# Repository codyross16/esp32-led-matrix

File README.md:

# ESP32 LED Matrix

Custom ESP32-S3 PCB with an 8x8 addressable LED matrix and push buttons, designed in KiCad and assembled by JLCPCB. Built to play simple one-button games like the Chrome Dino game.

Full schematic: [schematic.pdf](docs/schematic.pdf)

## Hardware
- ESP32-S3-MINI-1 (N8) microcontroller
- 64 SK6812MINI-E reverse-mount RGB LEDs in a serpentine chain
- USB-C power and programming, with 5.1k CC resistors
- SN74AHCT1G125 level shifter (3.3V to 5V LED data)
- AP7361C 3.3V LDO, SD05 TVS protection, 1000µF bulk cap
- 3 buttons: BOOT, RESET, and INPUT (game control)

## Repo layout
- `hardware/` KiCad project (schematic and PCB)
- `hardware/fab/` Gerbers, BOM, and CPL files for JLCPCB
- `firmware/` ESP32 code (coming soon)
- `docs/` Schematic PDF and images

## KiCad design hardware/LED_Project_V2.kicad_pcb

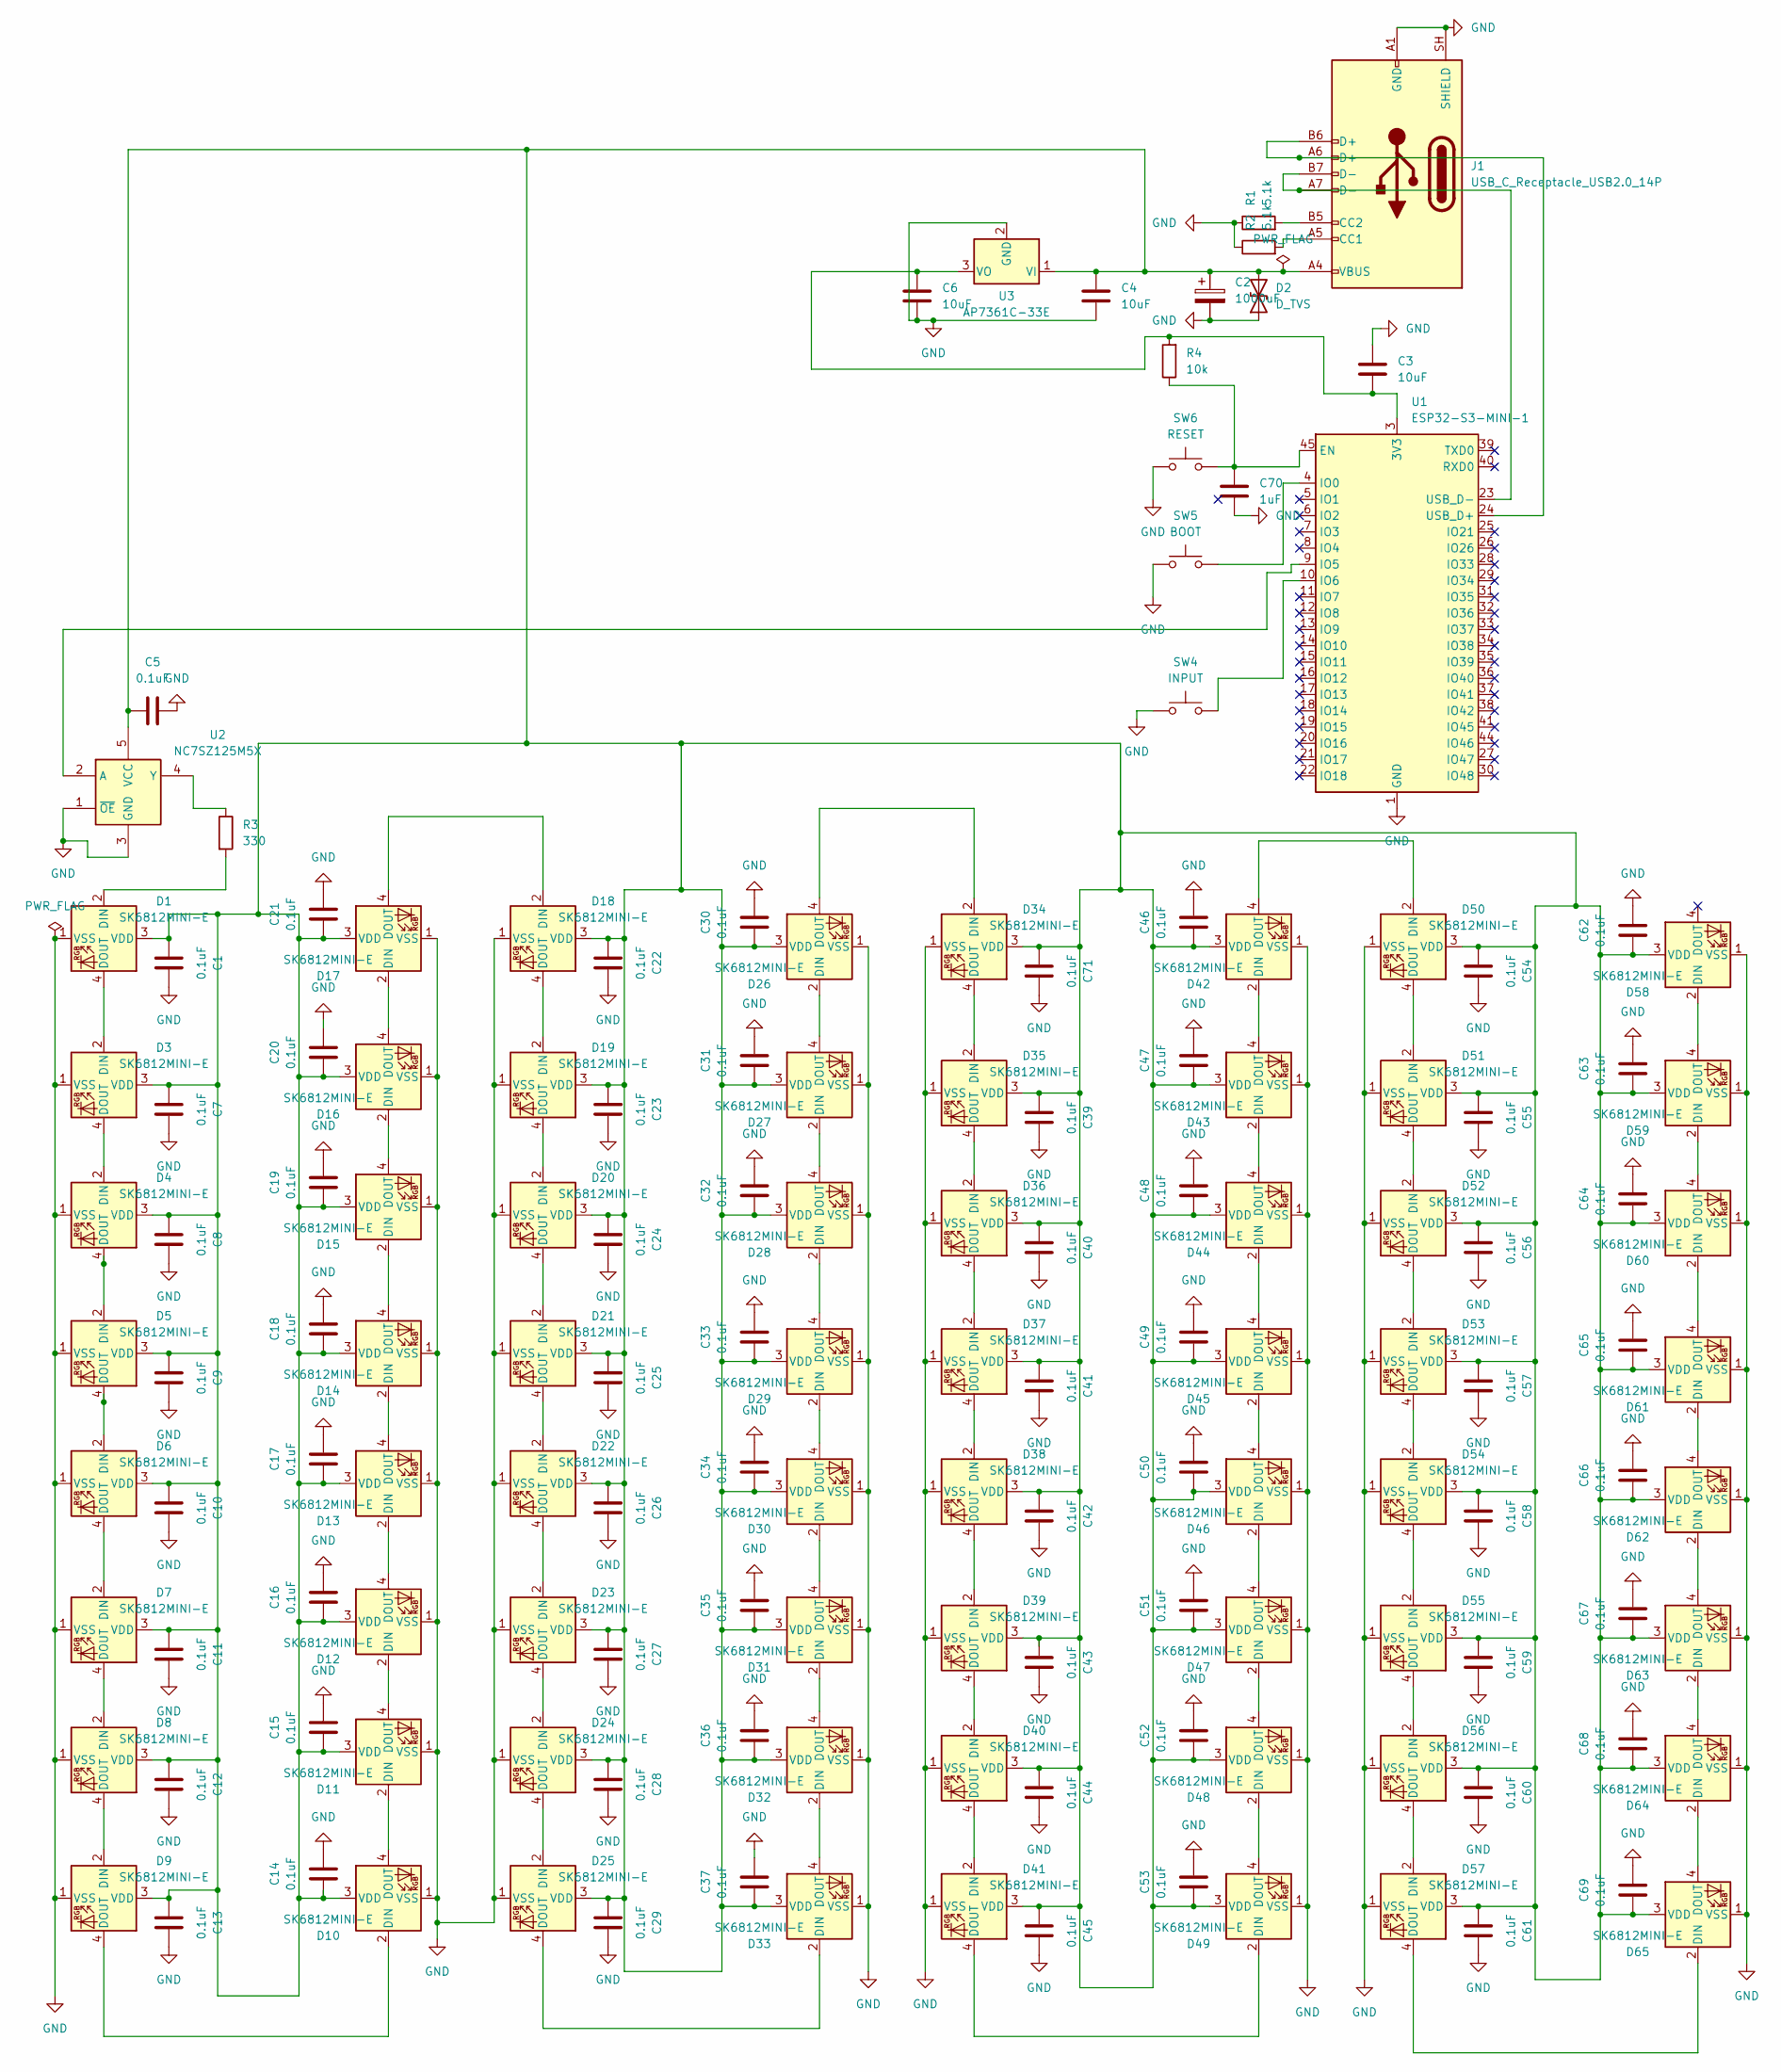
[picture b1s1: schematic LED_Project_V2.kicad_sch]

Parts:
C1, C5, C7, C8, C9, C10, C11, C12, C13, C14, C15, C16, C17, C18, C19, C20, C21, C22, C23, C24, C25, C26, C27, C28, C29, C30, C31, C32, C33, C34, C35, C36, C37, C39, C40, C41, C42, C43, C44, C45, C46, C47, C48, C49, C50, C51, C52, C53, C54, C55, C56, C57, C58, C59, C60, C61, C62, C63, C64, C65, C66, C67, C68, C69, C71: 0.1uF; C_0402_1005Metric
C2: 1000uF; CP_Elec_8x10
C3, C4, C6: 10uF; C_0402_1005Metric
C70: 1uF; C_0402_1005Metric
D1, D3, D4, D5, D6, D7, D8, D9, D10, D11, D12, D13, D14, D15, D16, D17, D18, D19, D20, D21, D22, D23, D24, D25, D26, D27, D28, D29, D30, D31, D32, D33, D34, D35, D36, D37, D38, D39, D40, D41, D42, D43, D44, D45, D46, D47, D48, D49, D50, D51, D52, D53, D54, D55, D56, D57, D58, D59, D60, D61, D62, D63, D64, D65: SK6812MINI-E; LED_SK6812MINI-E_3.2x2.8mm_P1.5mm_ReverseMount
D2: D_TVS; D_SOD-323
J1: USB_C_Receptacle_USB2.0_14P; USB_C_Receptacle_HRO_TYPE-C-31-M-12
R1, R2: 5.1k; R_0603_1608Metric
R3: 330; R_0603_1608Metric
R4: 10k; R_0603_1608Metric
SW4: INPUT; SW_SPST_Omron_B3FS-101xP
SW5: BOOT; SW_SPST_Omron_B3FS-101xP
SW6: RESET; SW_SPST_Omron_B3FS-101xP
U1: ESP32-S3-MINI-1; ESP32-S2-MINI-1
U2: NC7SZ125M5X; SOT-23-5
U3: AP7361C-33E; SOT-223-3_TabPin2

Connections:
GND: C1.2, C2.2, C3.2, C4.1, C5.2, C6.1, C7.2, C8.2, C9.2, C10.2, C11.2, C12.2, C13.2, C14.2, C15.2, C16.2, C17.2, C18.2, C19.2, C20.2, C21.2, C22.2, C23.2, C24.2, C25.2, C26.2, C27.2, C28.2, C29.2, C30.2, C31.2, C32.2, C33.2, C34.2, C35.2, C36.2, C37.2, C39.2, C40.2, C41.2, C42.2, C43.2, C44.2, C45.2, C46.2, C47.2, C48.2, C49.2, C50.2, C51.2, C52.2, C53.2, C54.2, C55.2, C56.2, C57.2, C58.2, C59.2, C60.2, C61.2, C62.2, C63.2, C64.2, C65.2, C66.2, C67.2, C68.2, C69.2, C70.2, C71.2, D1.1 (VSS), D2.1 (A1), D3.1 (VSS), D4.1 (VSS), D5.1 (VSS), D6.1 (VSS), D7.1 (VSS), D8.1 (VSS), D9.1 (VSS), D10.1 (VSS), D11.1 (VSS), D12.1 (VSS), D13.1 (VSS), D14.1 (VSS), D15.1 (VSS), D16.1 (VSS), D17.1 (VSS), D18.1 (VSS), D19.1 (VSS), D20.1 (VSS), D21.1 (VSS), D22.1 (VSS), D23.1 (VSS), D24.1 (VSS), D25.1 (VSS), D26.1 (VSS), D27.1 (VSS), D28.1 (VSS), D29.1 (VSS), D30.1 (VSS), D31.1 (VSS), D32.1 (VSS), D33.1 (VSS), D34.1 (VSS), D35.1 (VSS), D36.1 (VSS), D37.1 (VSS), D38.1 (VSS), D39.1 (VSS), D40.1 (VSS), D41.1 (VSS), D42.1 (VSS), D43.1 (VSS), D44.1 (VSS), D45.1 (VSS), D46.1 (VSS), D47.1 (VSS), D48.1 (VSS), D49.1 (VSS), D50.1 (VSS), D51.1 (VSS), D52.1 (VSS), D53.1 (VSS), D54.1 (VSS), D55.1 (VSS), D56.1 (VSS), D57.1 (VSS), D58.1 (VSS), D59.1 (VSS), D60.1 (VSS), D61.1 (VSS), D62.1 (VSS), D63.1 (VSS), D64.1 (VSS), D65.1 (VSS), J1.A1 (GND), J1.A12 (GND), J1.B1 (GND), J1.B12 (GND), J1.SH (SHIELD), R1.1, R2.1, SW4.1, SW5.1, SW6.1, U1.1 (GND), U1.2 (GND), U1.42 (GND), U1.43 (GND), U1.46 (GND), U1.47 (GND), U1.48 (GND), U1.49 (GND), U1.50 (GND), U1.51 (GND), U1.52 (GND), U1.53 (GND), U1.54 (GND), U1.55 (GND), U1.56 (GND), U1.57 (GND), U1.58 (GND), U1.59 (GND), U1.60 (GND), U1.61 (GND), U1.62 (GND), U1.63 (GND), U1.64 (GND), U1.65 (GND), U2.1 (~OE), U2.3 (GND), U3.2 (GND)
unnamed: D1.2 (DIN), R3.2
unnamed: D1.4 (DOUT), D3.2 (DIN)
unnamed: C1.1, C2.1, C4.2, C5.1, C7.1, C8.1, C9.1, C10.1, C11.1, C12.1, C13.1, C14.1, C15.1, C16.1, C17.1, C18.1, C19.1, C20.1, C21.1, C22.1, C23.1, C24.1, C25.1, C26.1, C27.1, C28.1, C29.1, C30.1, C31.1, C32.1, C33.1, C34.1, C35.1, C36.1, C37.1, C39.1, C40.1, C41.1, C42.1, C43.1, C44.1, C45.1, C46.1, C47.1, C48.1, C49.1, C50.1, C51.1, C52.1, C53.1, C54.1, C55.1, C56.1, C57.1, C58.1, C59.1, C60.1, C61.1, C62.1, C63.1, C64.1, C65.1, C66.1, C67.1, C68.1, C69.1, C71.1, D1.3 (VDD), D2.2 (A2), D3.3 (VDD), D4.3 (VDD), D5.3 (VDD), D6.3 (VDD), D7.3 (VDD), D8.3 (VDD), D9.3 (VDD), D10.3 (VDD), D11.3 (VDD), D12.3 (VDD), D13.3 (VDD), D14.3 (VDD), D15.3 (VDD), D16.3 (VDD), D17.3 (VDD), D18.3 (VDD), D19.3 (VDD), D20.3 (VDD), D21.3 (VDD), D22.3 (VDD), D23.3 (VDD), D24.3 (VDD), D25.3 (VDD), D26.3 (VDD), D27.3 (VDD), D28.3 (VDD), D29.3 (VDD), D30.3 (VDD), D31.3 (VDD), D32.3 (VDD), D33.3 (VDD), D34.3 (VDD), D35.3 (VDD), D36.3 (VDD), D37.3 (VDD), D38.3 (VDD), D39.3 (VDD), D40.3 (VDD), D41.3 (VDD), D42.3 (VDD), D43.3 (VDD), D44.3 (VDD), D45.3 (VDD), D46.3 (VDD), D47.3 (VDD), D48.3 (VDD), D49.3 (VDD), D50.3 (VDD), D51.3 (VDD), D52.3 (VDD), D53.3 (VDD), D54.3 (VDD), D55.3 (VDD), D56.3 (VDD), D57.3 (VDD), D58.3 (VDD), D59.3 (VDD), D60.3 (VDD), D61.3 (VDD), D62.3 (VDD), D63.3 (VDD), D64.3 (VDD), D65.3 (VDD), J1.A4 (VBUS), J1.A9 (VBUS), J1.B4 (VBUS), J1.B9 (VBUS), U2.5 (VCC), U3.1 (VI)
unnamed: D3.4 (DOUT), D4.2 (DIN)
unnamed: D4.4 (DOUT), D5.2 (DIN)
unnamed: D5.4 (DOUT), D6.2 (DIN)
unnamed: D6.4 (DOUT), D7.2 (DIN)
unnamed: D7.4 (DOUT), D8.2 (DIN)
unnamed: D8.4 (DOUT), D9.2 (DIN)
unnamed: D9.4 (DOUT), D10.2 (DIN)
unnamed: D10.4 (DOUT), D11.2 (DIN)
unnamed: D11.4 (DOUT), D12.2 (DIN)
unnamed: D12.4 (DOUT), D13.2 (DIN)
unnamed: D13.4 (DOUT), D14.2 (DIN)
unnamed: D14.4 (DOUT), D15.2 (DIN)
unnamed: D15.4 (DOUT), D16.2 (DIN)
unnamed: D16.4 (DOUT), D17.2 (DIN)
unnamed: D17.4 (DOUT), D18.2 (DIN)
unnamed: D18.4 (DOUT), D19.2 (DIN)
unnamed: D19.4 (DOUT), D20.2 (DIN)
unnamed: D20.4 (DOUT), D21.2 (DIN)
unnamed: D21.4 (DOUT), D22.2 (DIN)
unnamed: D22.4 (DOUT), D23.2 (DIN)
unnamed: D23.4 (DOUT), D24.2 (DIN)
unnamed: D24.4 (DOUT), D25.2 (DIN)
unnamed: D25.4 (DOUT), D33.2 (DIN)
unnamed: D26.2 (DIN), D27.4 (DOUT)
unnamed: D26.4 (DOUT), D34.2 (DIN)
unnamed: D27.2 (DIN), D28.4 (DOUT)
unnamed: D28.2 (DIN), D29.4 (DOUT)
unnamed: D29.2 (DIN), D30.4 (DOUT)
unnamed: D30.2 (DIN), D31.4 (DOUT)
unnamed: D31.2 (DIN), D32.4 (DOUT)
unnamed: D32.2 (DIN), D33.4 (DOUT)
unnamed: D34.4 (DOUT), D35.2 (DIN)
unnamed: D35.4 (DOUT), D36.2 (DIN)
unnamed: D36.4 (DOUT), D37.2 (DIN)
unnamed: D37.4 (DOUT), D38.2 (DIN)
unnamed: D38.4 (DOUT), D39.2 (DIN)
unnamed: D39.4 (DOUT), D40.2 (DIN)
unnamed: D40.4 (DOUT), D41.2 (DIN)
unnamed: D41.4 (DOUT), D49.2 (DIN)
unnamed: D42.2 (DIN), D43.4 (DOUT)
unnamed: D42.4 (DOUT), D50.2 (DIN)
unnamed: D43.2 (DIN), D44.4 (DOUT)
unnamed: D44.2 (DIN), D45.4 (DOUT)
unnamed: D45.2 (DIN), D46.4 (DOUT)
unnamed: D46.2 (DIN), D47.4 (DOUT)
unnamed: D47.2 (DIN), D48.4 (DOUT)
unnamed: D48.2 (DIN), D49.4 (DOUT)
unnamed: D50.4 (DOUT), D51.2 (DIN)
unnamed: D51.4 (DOUT), D52.2 (DIN)
unnamed: D52.4 (DOUT), D53.2 (DIN)
unnamed: D53.4 (DOUT), D54.2 (DIN)
unnamed: D54.4 (DOUT), D55.2 (DIN)
unnamed: D55.4 (DOUT), D56.2 (DIN)
unnamed: D56.4 (DOUT), D57.2 (DIN)
unnamed: D57.4 (DOUT), D65.2 (DIN)
unnamed: D58.2 (DIN), D59.4 (DOUT)
unnamed: D59.2 (DIN), D60.4 (DOUT)
unnamed: D60.2 (DIN), D61.4 (DOUT)
unnamed: D61.2 (DIN), D62.4 (DOUT)
unnamed: D62.2 (DIN), D63.4 (DOUT)
unnamed: D63.2 (DIN), D64.4 (DOUT)
unnamed: D64.2 (DIN), D65.4 (DOUT)
unnamed: J1.A5 (CC1), R2.2
unnamed: J1.B5 (CC2), R1.2
unnamed: C3.1, C6.2, R4.2, U1.3 (3V3), U3.3 (VO)
unnamed: C70.1, R4.1, SW6.2, U1.45 (EN)
unnamed: SW5.2, U1.4 (IO0)
unnamed: U1.9 (IO5), U2.2 (A)
unnamed: SW4.2, U1.10 (IO6)
unnamed: J1.A6 (D+), J1.B6 (D+), U1.24 (USB_D+)
unnamed: J1.A7 (D-), J1.B7 (D-), U1.23 (USB_D-)
unnamed: R3.1, U2.4 (Y)

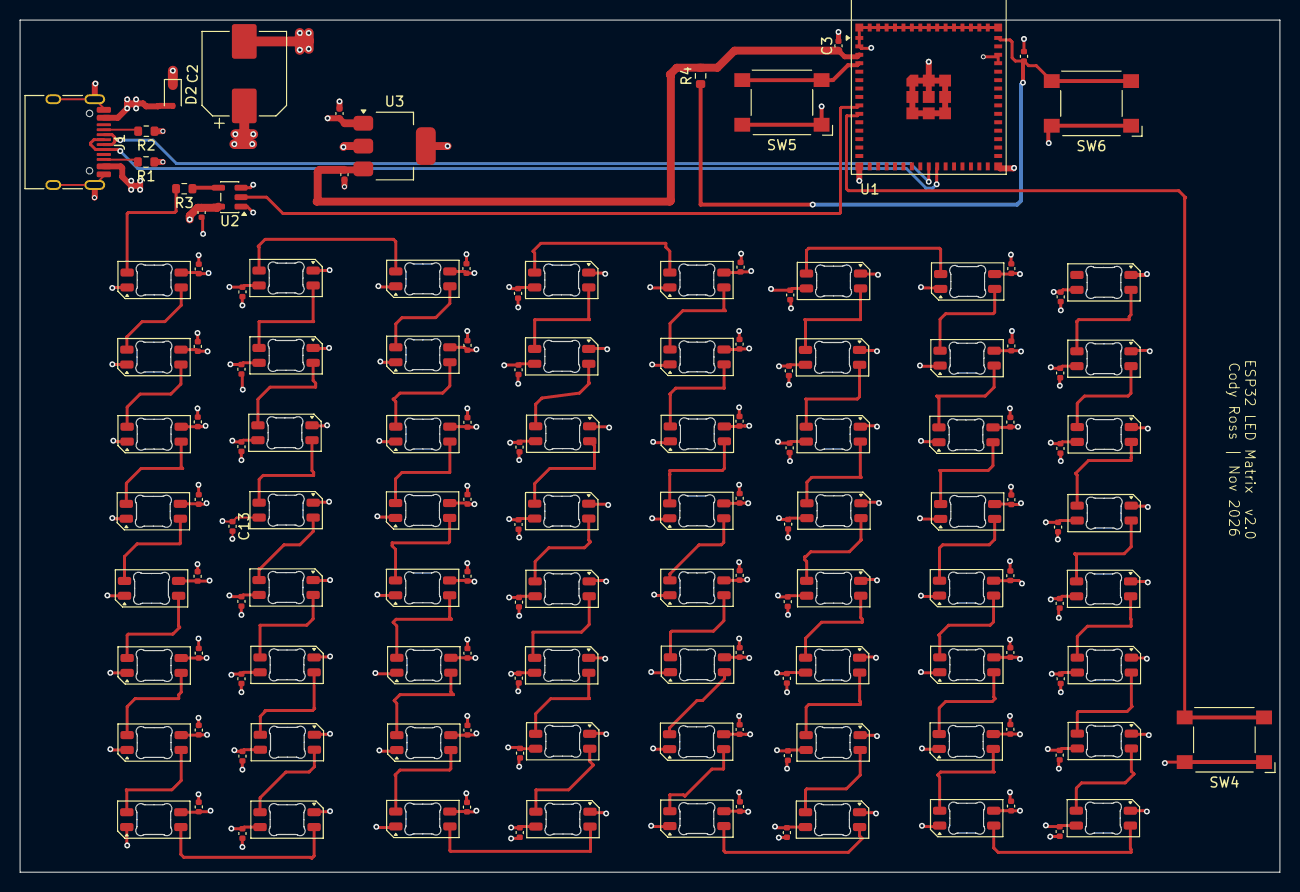
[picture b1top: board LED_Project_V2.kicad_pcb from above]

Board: 4 copper layers, 127.0 x 85.9 mm, 146 parts (0 on the bottom side), 76 nets.

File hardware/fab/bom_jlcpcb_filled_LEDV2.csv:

Comment,Designator,Footprint,LCSC Part #
0.1uF,"C1, C5, C7, C8, C9, C10, C11, C12, C13, C14, C15, C16, C17, C18, C19, C20, C21, C22, C23, C24, C25, C26, C27, C28, C29, C30, C31, C32, C33, C34, C35, C36, C37, C39, C40, C41, C42, C43, C44, C45, C46, C47, C48, C49, C50, C51, C52, C53, C54, C55, C56, C57, C58, C59, C60, C61, C62, C63, C64, C65, C66, C67, C68, C69, C71",C_0402_1005Metric,C1525
1000uF,C2,CP_Elec_8x10,C5246577
10uF 10V,"C4, C6",C_0402_1005Metric,C315248
10uF,C3,C_0402_1005Metric,C15525
1uF,C70,C_0402_1005Metric,C52923
SK6812MINI-E,"D1, D3, D4, D5, D6, D7, D8, D9, D10, D11, D12, D13, D14, D15, D16, D17, D18, D19, D20, D21, D22, D23, D24, D25, D26, D27, D28, D29, D30, D31, D32, D33, D34, D35, D36, D37, D38, D39, D40, D41, D42, D43, D44, D45, D46, D47, D48, D49, D50, D51, D52, D53, D54, D55, D56, D57, D58, D59, D60, D61, D62, D63, D64, D65",LED_SK6812MINI-E_3.2x2.8mm_P1.5mm_ReverseMount,C5149201
D_TVS,D2,D_SOD-323,C502527
USB_C_Receptacle_USB2.0_14P,J1,USB_C_Receptacle_HRO_TYPE-C-31-M-12,C165948
5.1k,"R1, R2",R_0603_1608Metric,C23186
330,R3,R_0603_1608Metric,C23138
10k,R4,R_0603_1608Metric,C25804
INPUT,SW4,SW_SPST_Omron_B3FS-101xP,C231324
BOOT,SW5,SW_SPST_Omron_B3FS-101xP,C231324
RESET,SW6,SW_SPST_Omron_B3FS-101xP,C231324
ESP32-S3-MINI-1,U1,ESP32-S2-MINI-1,C2913206
SN74AHCT1G125DBVR,U2,SOT-23-5,C7484
AP7361C-33E,U3,SOT-223-3_TabPin2,C500795
